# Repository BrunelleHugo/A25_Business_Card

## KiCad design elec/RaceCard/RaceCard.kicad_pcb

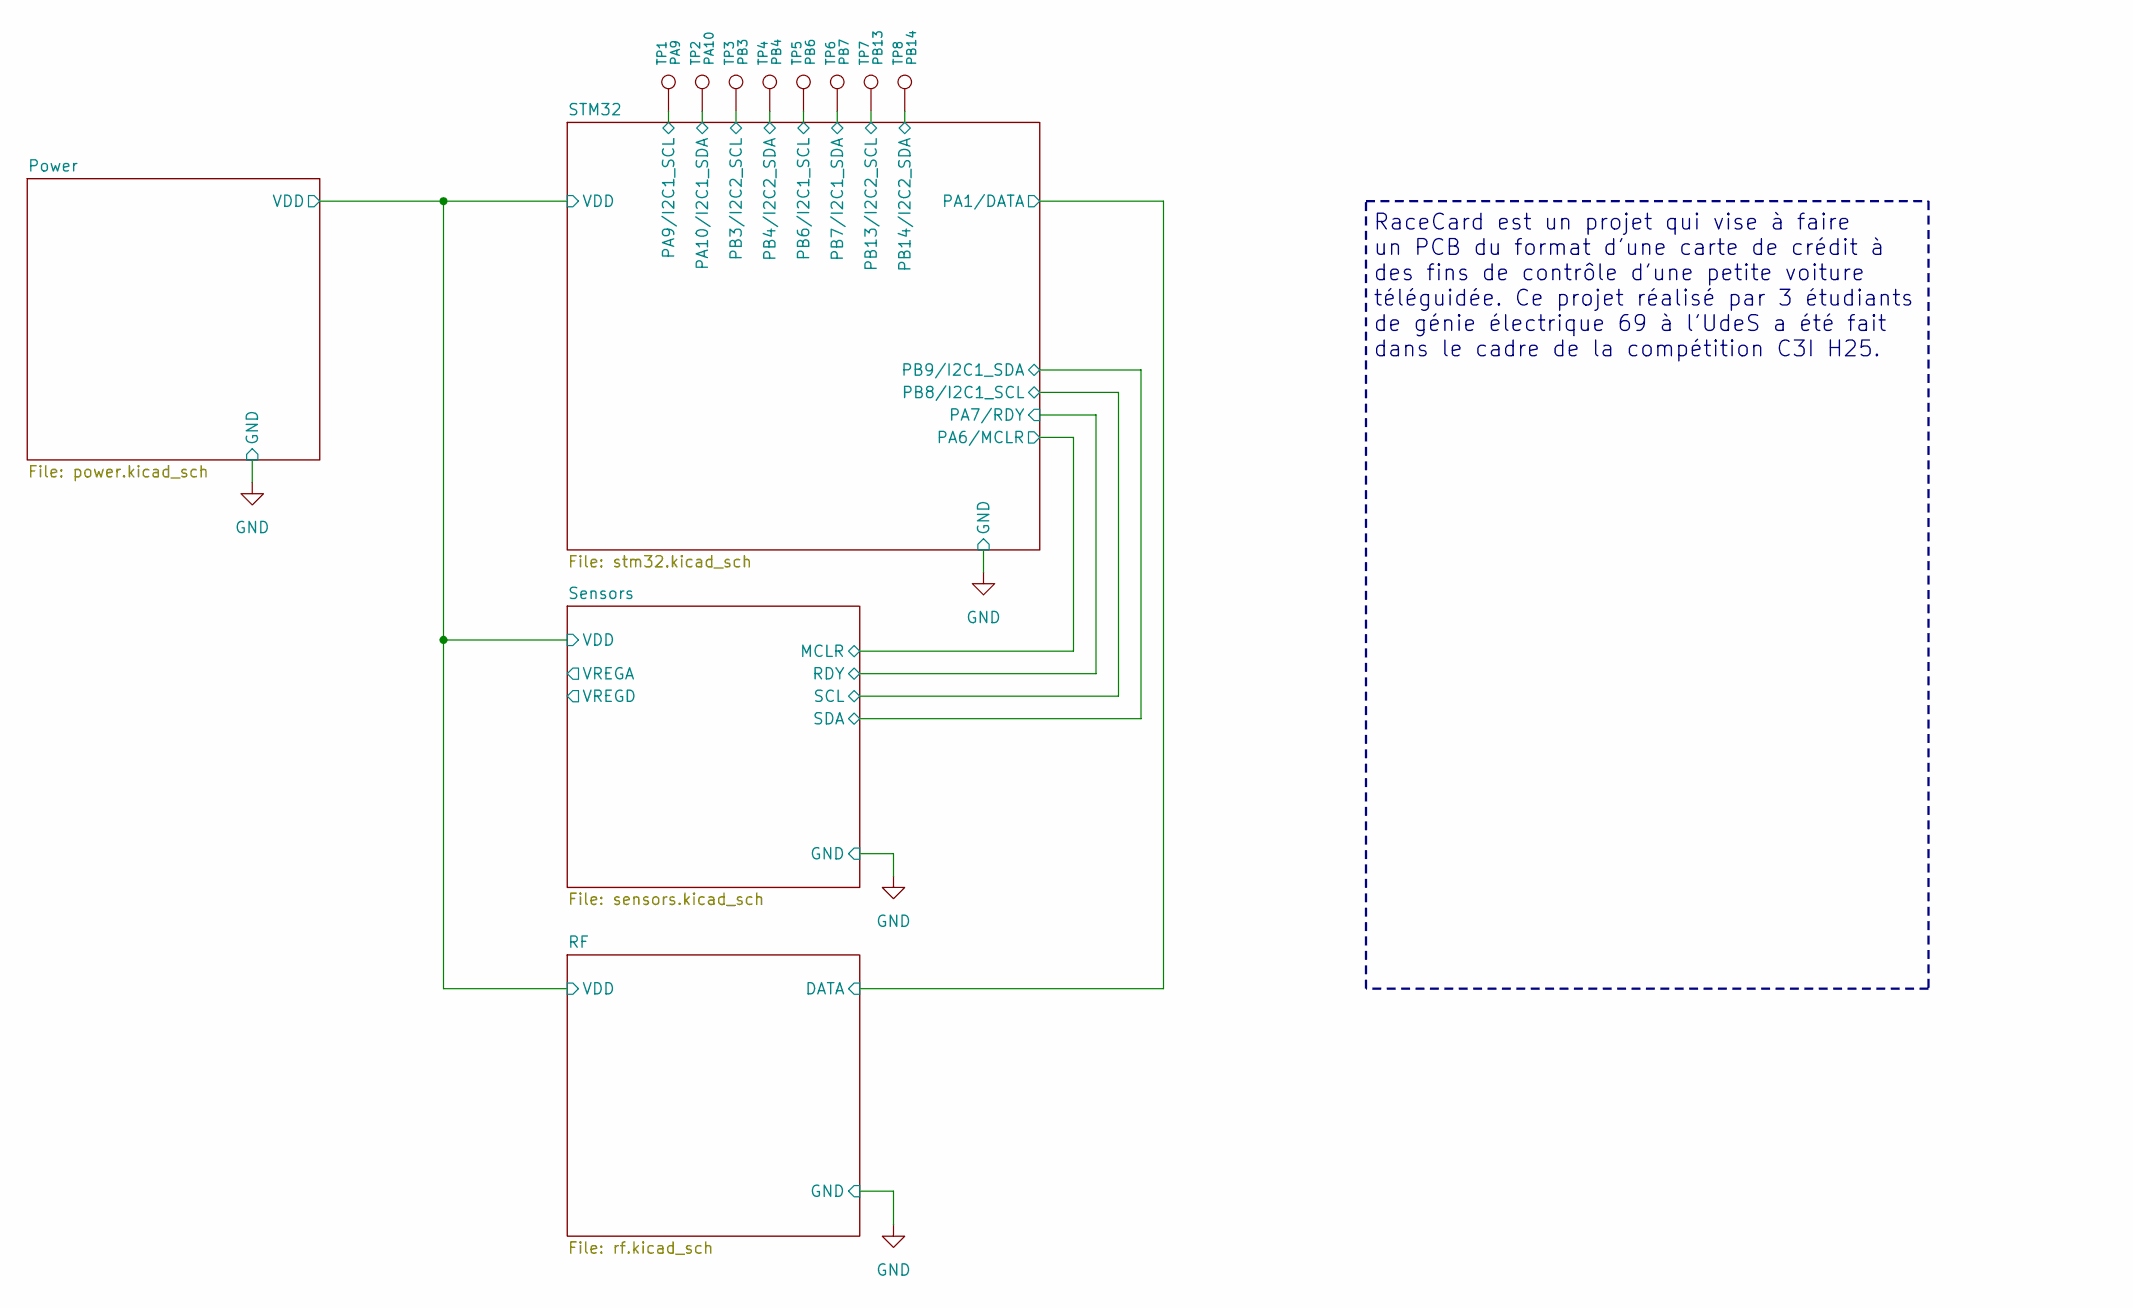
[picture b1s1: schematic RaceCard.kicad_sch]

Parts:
TP1: PA9; TestPoint_Pad_2.0x2.0mm
TP2: PA10; TestPoint_Pad_2.0x2.0mm
TP3: PB3; TestPoint_Pad_2.0x2.0mm
TP4: PB4; TestPoint_Pad_2.0x2.0mm
TP5: PB6; TestPoint_Pad_2.0x2.0mm
TP6: PB7; TestPoint_Pad_2.0x2.0mm
TP7: PB13; TestPoint_Pad_2.0x2.0mm
TP8: PB14; TestPoint_Pad_2.0x2.0mm

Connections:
/STM32/PA9/I2C1_SCL: TP1.1; also elsewhere on the board
/STM32/PA10/I2C1_SDA: TP2.1; also elsewhere on the board
/STM32/PB3/I2C2_SCL: TP3.1; also elsewhere on the board
/STM32/PB4/I2C2_SDA: TP4.1; also elsewhere on the board
/STM32/PB6/I2C1_SCL: TP5.1; also elsewhere on the board
/STM32/PB7/I2C1_SDA: TP6.1; also elsewhere on the board
/STM32/PB13/I2C2_SCL: TP7.1; also elsewhere on the board
/STM32/PB14/I2C2_SDA: TP8.1; also elsewhere on the board

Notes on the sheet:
RaceCard est un projet qui vise à faire un PCB du format d'une carte de crédit à des fins de contrôle d'une petite voiture téléguidée. Ce projet réalisé par 3 étudiants de génie électrique 69 à l'UdeS a été fait dans le cadre de la compétition C3I H25.

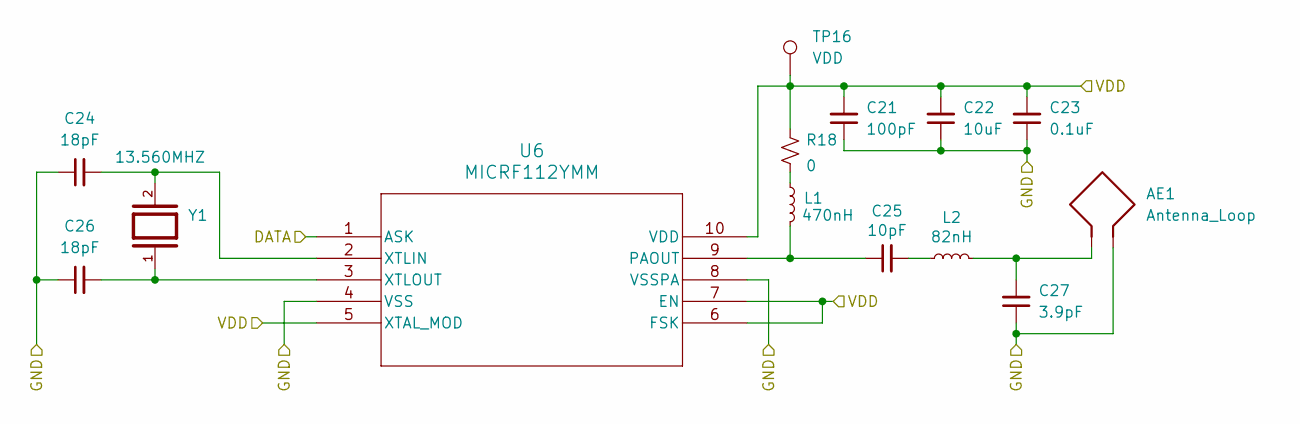
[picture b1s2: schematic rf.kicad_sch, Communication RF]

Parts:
AE1: Antenna_Loop
C21: 100pF; C_0603_1608Metric
C22: 10uF; C_0603_1608Metric
C23: 0.1uF; C_0603_1608Metric
C24, C26: 18pF; C_0603_1608Metric
C25: 10pF; C_0603_1608Metric
C27: 3.9pF; C_0603_1608Metric
L1: 470nH; L_0603_1608Metric
L2: 82nH; L_0603_1608Metric
R18: 0; R_0603_1608Metric
TP16: VDD; TestPoint_THTPad_3.0x3.0mm_Drill1.5mm
U6: MICRF112YMM; MSOP10_MC_MCH
Y1: 13.560MHZ; XTAL_ABLS-13.560MHZ-10-R20-D-T; PARTREV 02.16.2021

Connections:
/Power/VDD: C21.2, C22.2, C23.2, R18.1, TP16.1, U6.5 (XTAL_MOD), U6.6 (FSK), U6.7 (EN), U6.10 (VDD); also elsewhere on the board
/RF/DATA: U6.1 (ASK); also elsewhere on the board
GND: C21.1, C22.1, C23.1, C24.1, C26.1, C27.1, U6.4 (VSS), U6.8 (VSSPA); also elsewhere on the board
unnamed: C27.2, L2.2
unnamed: C25.2, L2.1
unnamed: L1.1, R18.2
unnamed: C25.1, L1.2, U6.9 (PAOUT)
unnamed: C24.2, U6.2 (XTLIN), Y1.2
unnamed: C26.2, U6.3 (XTLOUT), Y1.1

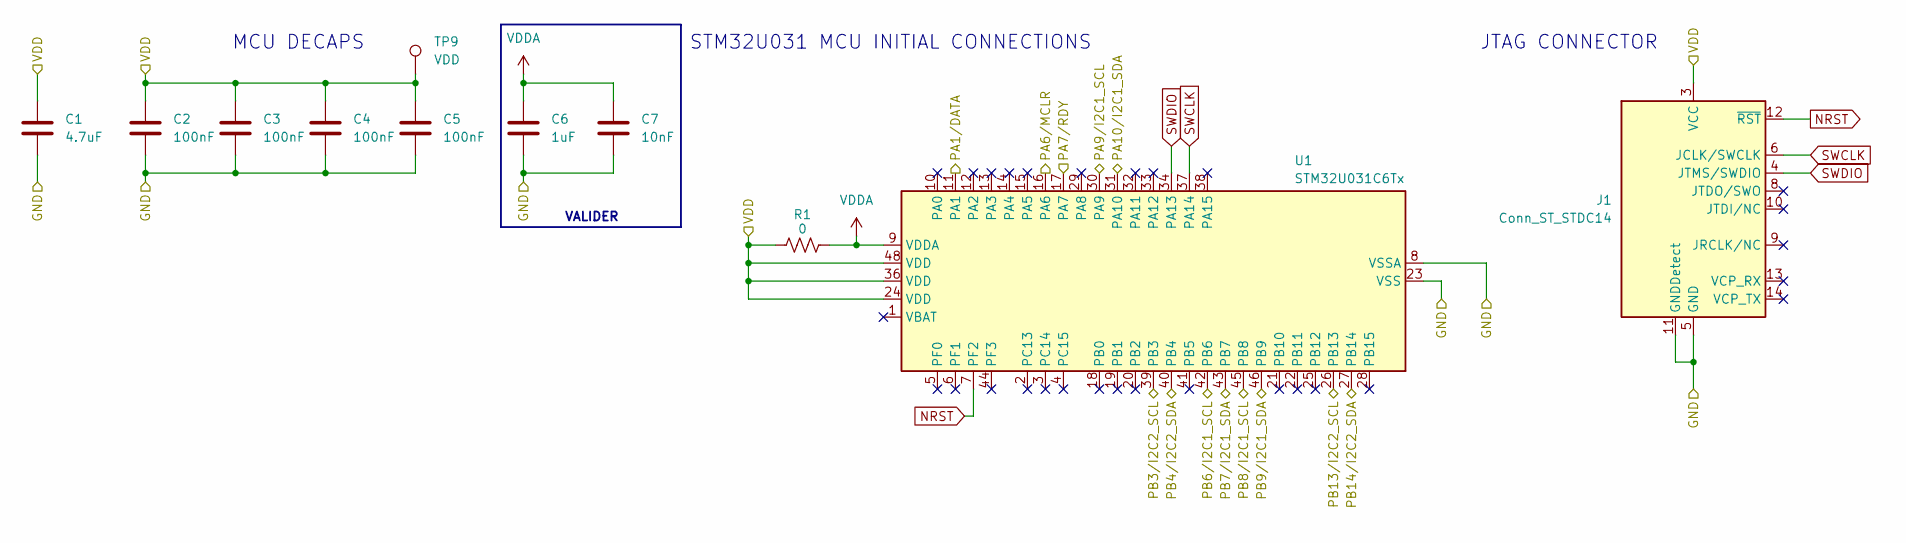
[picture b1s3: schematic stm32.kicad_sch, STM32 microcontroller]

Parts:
C1: 4.7uF; C_0603_1608Metric
C2, C3, C4, C5: 100nF; C_0603_1608Metric
C6: 1uF; C_0603_1608Metric
C7: 10nF; C_0603_1608Metric
J1: Conn_ST_STDC14; CONN_3020-14-0300-00_CNC
R1: 0; R_0603_1608Metric
TP9: VDD; TestPoint_THTPad_3.0x3.0mm_Drill1.5mm
U1: STM32U031C6Tx; LQFP-48_7x7mm_P0.5mm

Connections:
/Power/VDD: C1.1, C2.1, C3.1, C4.1, C5.1, J1.3 (VCC), R1.1, TP9.1, U1.24 (VDD), U1.36 (VDD), U1.48 (VDD); also elsewhere on the board
/RF/DATA: U1.11 (PA1); also elsewhere on the board
/STM32/PA6/MCLR: U1.16 (PA6); also elsewhere on the board
/STM32/PA7/RDY: U1.17 (PA7); also elsewhere on the board
/STM32/PA9/I2C1_SCL: U1.30 (PA9); also elsewhere on the board
/STM32/PA10/I2C1_SDA: U1.31 (PA10); also elsewhere on the board
/STM32/PB3/I2C2_SCL: U1.39 (PB3); also elsewhere on the board
/STM32/PB4/I2C2_SDA: U1.40 (PB4); also elsewhere on the board
/STM32/PB6/I2C1_SCL: U1.42 (PB6); also elsewhere on the board
/STM32/PB7/I2C1_SDA: U1.43 (PB7); also elsewhere on the board
/STM32/PB8/I2C1_SCL: U1.45 (PB8); also elsewhere on the board
/STM32/PB9/I2C1_SDA: U1.46 (PB9); also elsewhere on the board
/STM32/PB13/I2C2_SCL: U1.26 (PB13); also elsewhere on the board
/STM32/PB14/I2C2_SDA: U1.27 (PB14); also elsewhere on the board
GND: C1.2, C2.2, C3.2, C4.2, C5.2, C6.2, C7.2, J1.5 (GND), J1.7 (GND), J1.11 (GNDDetect), U1.8 (VSSA), U1.23 (VSS), U1.35 (VSS), U1.47 (VSS); also elsewhere on the board
NRST: J1.12 (~RST), U1.7 (PF2)
SWCLK: J1.6 (JCLK/SWCLK), U1.37 (PA14)
SWDIO: J1.4 (JTMS/SWDIO), U1.34 (PA13)
VDDA: C6.1, C7.1, R1.2, U1.9 (VDDA)

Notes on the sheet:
MCU DECAPS
JTAG CONNECTOR
VALIDER
STM32U031 MCU INITIAL CONNECTIONS

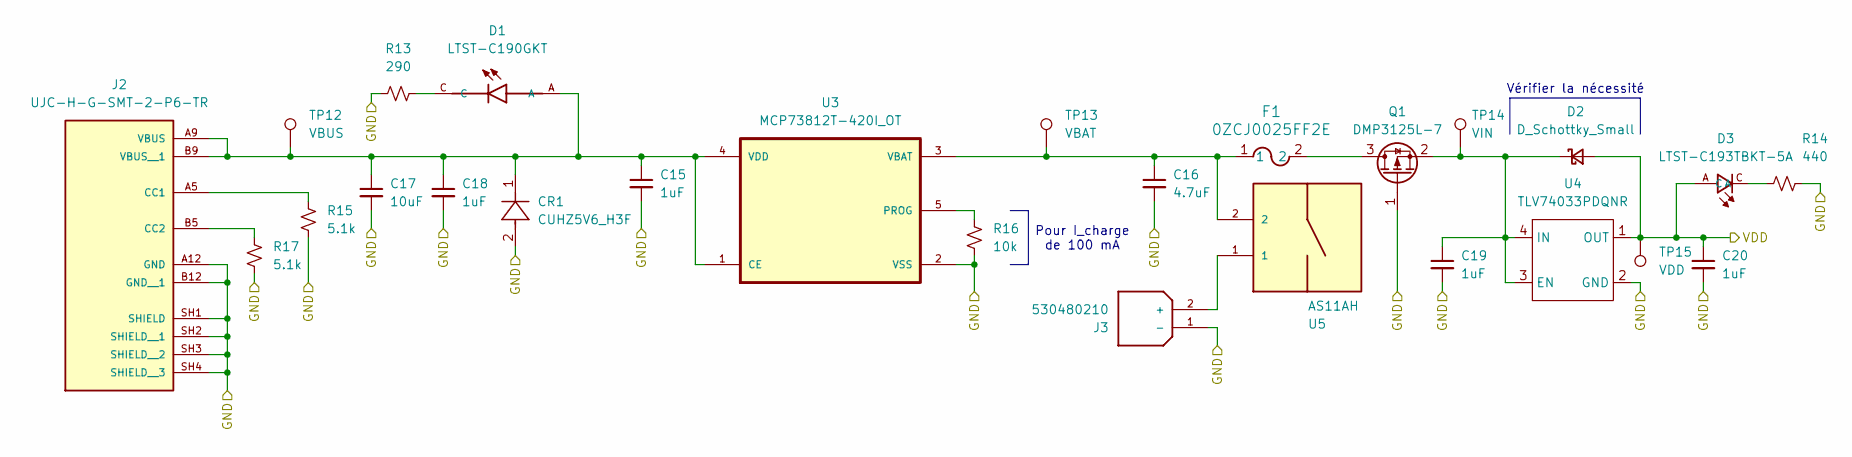
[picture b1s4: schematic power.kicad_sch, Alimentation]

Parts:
C15, C18, C19, C20: 1uF; C_0603_1608Metric
C16: 4.7uF; C_0603_1608Metric
C17: 10uF; C_0603_1608Metric
CR1: CUHZ5V6_H3F; SOD-323HEUS2H_TOS
D1: LTST-C190GKT; LEDM1608X80
D2: D_Schottky_Small; D_0603_1608Metric
D3: LTST-C193TBKT-5A; LEDM1608X80
F1: 0ZCJ0025FF2E; 0ZCJ_BEL
J2: UJC-H-G-SMT-2-P6-TR; SAMESKY_UJC-H-G-SMT-2-P6-TR; PARTREV 1.0
J3: 530480210; MOLEX_530480210; PARTREV A
Q1: DMP3125L-7; SOT91P240X110-3N
R13: 290; R_0603_1608Metric
R14: 440; R_0603_1608Metric
R15, R17: 5.1k; R_0603_1608Metric
R16: 10k; R_0603_1608Metric
TP12: VBUS; TestPoint_THTPad_3.0x3.0mm_Drill1.5mm
TP13: VBAT; TestPoint_THTPad_3.0x3.0mm_Drill1.5mm
TP14: VIN; TestPoint_THTPad_3.0x3.0mm_Drill1.5mm
TP15: VDD; TestPoint_THTPad_3.0x3.0mm_Drill1.5mm
U3: MCP73812T-420I_OT; SOT95P280X145-5N
U4: TLV74033PDQNR; SUP_TPS3831L30DQNR
U5: AS11AH

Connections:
/Power/VDD: C20.1, D2.2 (A), D3.A, TP15.1, U4.1 (OUT); also elsewhere on the board
GND: C15.2, C16.2, C17.2, C18.2, C19.2, C20.2, CR1.2, J2.A12 (GND), J2.B12 (GND__1), J2.SH1 (SHIELD), J2.SH2 (SHIELD__1), J2.SH3 (SHIELD__2), J2.SH4 (SHIELD__3), J3.1 (-), Q1.1 (G), R13.1, R14.2, R15.1, R16.2, R17.2, U3.2 (VSS), U4.2 (GND); also elsewhere on the board
unnamed: D1.C, R13.2
unnamed: C19.1, D2.1 (K), Q1.2 (S), TP14.1, U4.3 (EN), U4.4 (IN)
unnamed: D3.C, R14.1
unnamed: J2.A5 (CC1), R15.2
unnamed: J2.B5 (CC2), R17.1
unnamed: C15.1, C17.1, C18.1, CR1.1, D1.A, J2.A9 (VBUS), J2.B9 (VBUS__1), TP12.1, U3.1 (CE), U3.4 (VDD)
unnamed: J3.2 (+), U5.1
unnamed: F1.2, Q1.3 (D)
unnamed: R16.1, U3.5 (PROG)
unnamed: C16.1, F1.1, TP13.1, U3.3 (VBAT), U5.2

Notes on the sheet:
Vérifier la nécessité
Pour I_charge de 100 mA

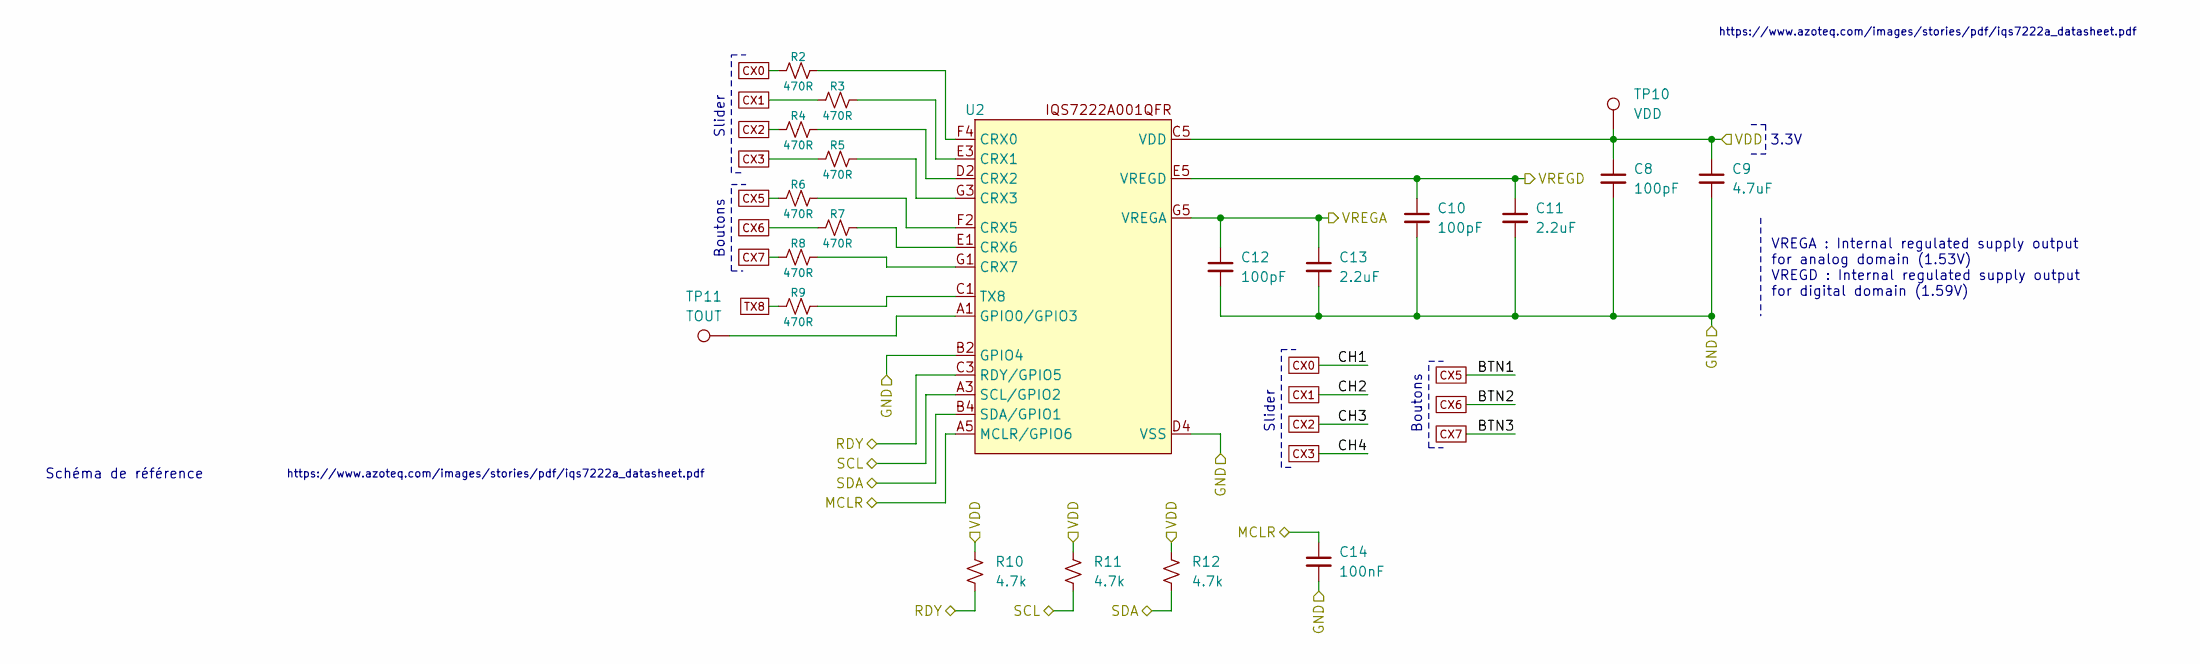
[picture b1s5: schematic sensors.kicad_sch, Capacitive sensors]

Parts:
C8, C10, C12: 100pF; C_0603_1608Metric
C9: 4.7uF; C_0603_1608Metric
C11, C13: 2.2uF; C_0603_1608Metric
C14: 100nF; C_0603_1608Metric
R2, R3, R4, R5, R6, R7, R8, R9: 470R; R_0603_1608Metric
R10, R11, R12: 4.7k; R_0603_1608Metric
TP10: VDD; TestPoint_THTPad_3.0x3.0mm_Drill1.5mm
TP11: TOUT; TestPoint_THTPad_3.0x3.0mm_Drill1.5mm
U2: IQS7222A001QFR; IQS7222A001CSR

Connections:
/Power/VDD: C8.1, C9.1, R10.1, R11.1, R12.1, TP10.1, U2.C5 (VDD); also elsewhere on the board
/STM32/PA6/MCLR: C14.1, U2.A5 (MCLR/GPIO6); also elsewhere on the board
/STM32/PA7/RDY: R10.2, U2.C3 (RDY/GPIO5); also elsewhere on the board
/STM32/PB8/I2C1_SCL: R11.2, U2.A3 (SCL/GPIO2); also elsewhere on the board
/STM32/PB9/I2C1_SDA: R12.2, U2.B4 (SDA/GPIO1); also elsewhere on the board
/Sensors/VREGA: C12.1, C13.1, U2.G5 (VREGA)
/Sensors/VREGD: C10.1, C11.1, U2.E5 (VREGD)
CX0: R2.1
CX1: R3.1
CX2: R4.1
CX3: R5.1
CX5: R6.1
CX6: R7.1
CX7: R8.1
GND: C8.2, C9.2, C10.2, C11.2, C12.2, C13.2, C14.2, U2.B2 (GPIO4), U2.D4 (VSS); also elsewhere on the board
unnamed: R2.2, U2.F4 (CRX0)
unnamed: R3.2, U2.E3 (CRX1)
unnamed: R4.2, U2.D2 (CRX2)
unnamed: R5.2, U2.G3 (CRX3)
unnamed: R6.2, U2.F2 (CRX5)
unnamed: R7.2, U2.E1 (CRX6)
unnamed: R8.2, U2.G1 (CRX7)
unnamed: TP11.1, U2.A1 (GPIO0/GPIO3)
unnamed: R9.2, U2.C1 (TX8)
TX8: R9.1

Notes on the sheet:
VREGA : Internal regulated supply output for analog domain (1.53V) VREGD : Internal regulated supply output for digital domain (1.59V)
Slider
Schéma de référence
https://www.azoteq.com/images/stories/pdf/iqs7222a_datasheet.pdf
Boutons
3.3V

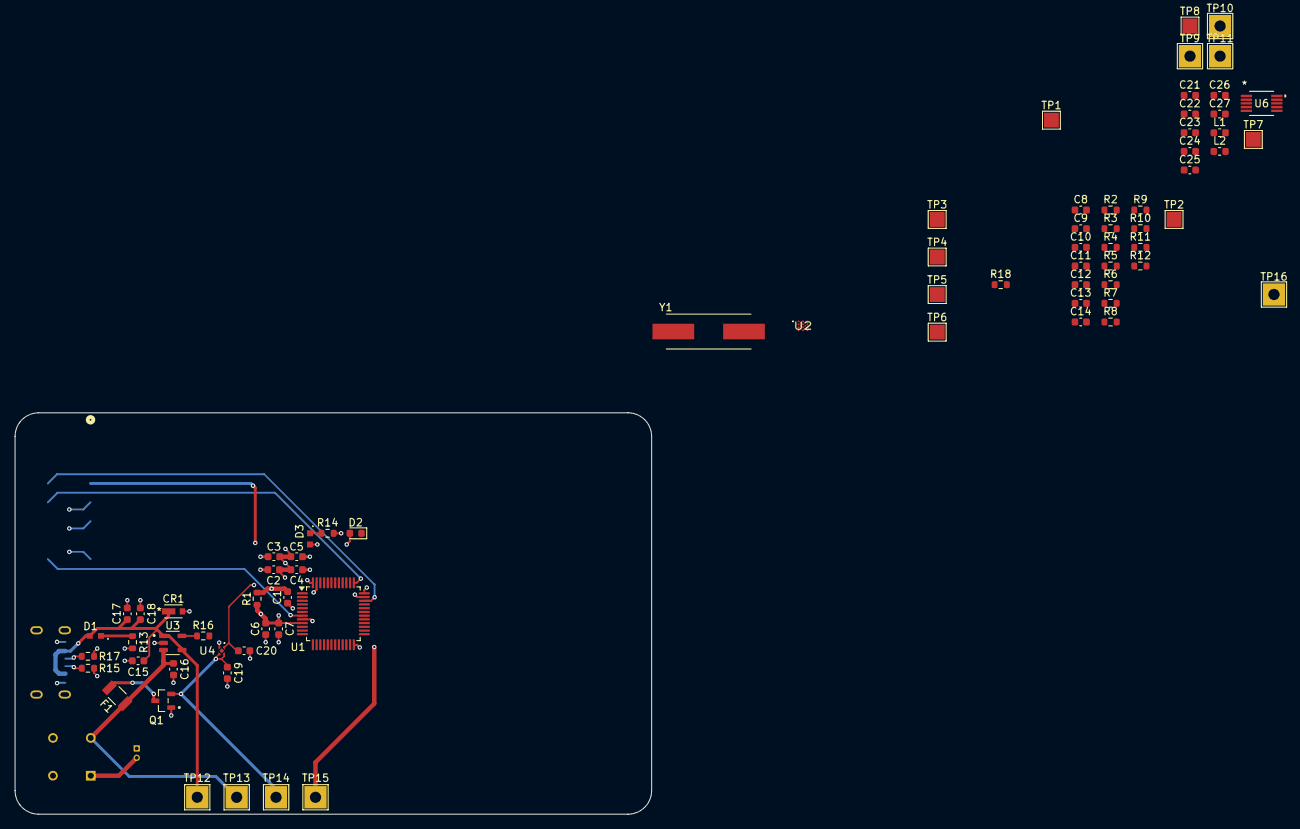
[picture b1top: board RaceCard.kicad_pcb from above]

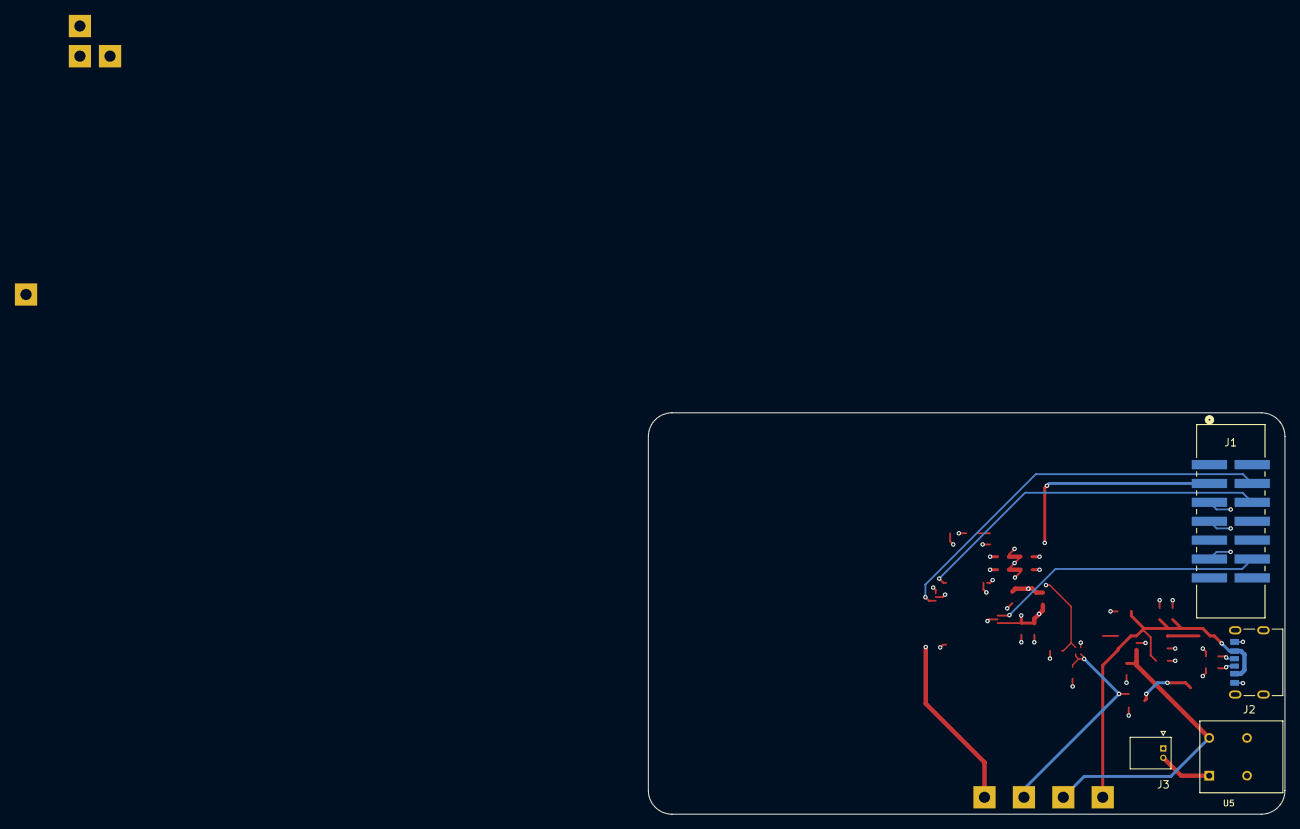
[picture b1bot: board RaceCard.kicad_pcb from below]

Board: 4 copper layers, 85.6 x 54.0 mm, 79 parts (4 on the bottom side), 46 nets.

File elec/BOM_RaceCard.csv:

Reference;Qty;Value;DNP;Exclude from BOM;Exclude from Board;Footprint;Datasheet
AE1;1;Antenna_Loop;;;;;~
C1,C9,C16;3;4.7uF;;;;Capacitor_SMD:C_0603_1608Metric;~
C2,C3,C4,C5,C14;5;100nF;;;;Capacitor_SMD:C_0603_1608Metric;~
C6,C15,C18,C19,C20;5;1uF;;;;Capacitor_SMD:C_0603_1608Metric;~
C7;1;10nF;;;;Capacitor_SMD:C_0603_1608Metric;~
C8,C10,C12,C21;4;100pF;;;;Capacitor_SMD:C_0603_1608Metric;~
C11,C13;2;2.2uF;;;;Capacitor_SMD:C_0603_1608Metric;~
C17,C22;2;10uF;;;;Capacitor_SMD:C_0603_1608Metric;~
C23;1;0.1uF;;;;Capacitor_SMD:C_0603_1608Metric;~
C24,C26;2;18pF;;;;Capacitor_SMD:C_0603_1608Metric;~
C25;1;10pF;;;;Capacitor_SMD:C_0603_1608Metric;~
C27;1;3.9pF;;;;Capacitor_SMD:C_0603_1608Metric;~
CR1;1;CUHZ5V6_H3F;;;;C3I_A25:SOD-323HEUS2H_TOS;https://toshiba.semicon-storage.com/info/docget.jsp?did=1415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
D1;1;LTST-C190GKT;;;;LTST-C190GKT:LEDM1608X80;
D2;1;D_Schottky_Small;;;;;~
D3;1;LTST-C193TBKT-5A;;;;LTST-C193TBKT-5A:0603;
F1;1;0ZCJ0025FF2E;;;;C3I_A25:0ZCJ_BEL;0ZCJ0025FF2E
J1;1;Conn_ST_STDC14;;;;C3I_A25:CONN_3020-14-0300-00_CNC;https://www.cnctech.us/pdfs/3020-XX-0300-00%20(9T).pdf
J2;1;UJC-H-G-SMT-2-P6-TR;;;;UJC-H-G-SMT-2-P6-TR:SAMESKY_UJC-H-G-SMT-2-P6-TR;
J3;1;530480210;;;;530480210:MOLEX_530480210;
L1;1;470nH;;;;Inductor_SMD:L_0603_1608Metric;~
L2;1;82nH;;;;Inductor_SMD:L_0603_1608Metric;~
Q1;1;DMP3125L-7;;;;C3I_A25:SOT91P240X110-3N;~
R1,R19;2;0;;;;Resistor_SMD:R_0603_1608Metric;~
R2,R3,R4,R5,R6,R7,R8,R9,R10;9;470R;;;;Resistor_SMD:R_0603_1608Metric;~
R11,R12,R13;3;4.7k;;;;Resistor_SMD:R_0603_1608Metric;~
R14;1;290;;;;Resistor_SMD:R_0603_1608Metric;~
R15;1;440;;;;Resistor_SMD:R_0603_1608Metric;~
R16,R18;2;5.1k;;;;Resistor_SMD:R_0603_1608Metric;~
R17;1;10k;;;;Resistor_SMD:R_0603_1608Metric;~
TP1,TP2,TP6,TP7;4;VDD;;;;TestPoint:TestPoint_THTPad_3.0x3.0mm_Drill1.5mm;~
TP3;1;VBUS;;;;TestPoint:TestPoint_THTPad_3.0x3.0mm_Drill1.5mm;~
TP4;1;VBAT;;;;TestPoint:TestPoint_THTPad_3.0x3.0mm_Drill1.5mm;~
TP5;1;VIN;;;;TestPoint:TestPoint_THTPad_3.0x3.0mm_Drill1.5mm;~
TP8;1;PA9;;;;TestPoint:TestPoint_Pad_2.0x2.0mm;~
TP9;1;PA10;;;;TestPoint:TestPoint_Pad_2.0x2.0mm;~
TP10;1;PB3;;;;TestPoint:TestPoint_Pad_2.0x2.0mm;~
TP11;1;PB4;;;;TestPoint:TestPoint_Pad_2.0x2.0mm;~
TP12;1;PB6;;;;TestPoint:TestPoint_Pad_2.0x2.0mm;~
TP13;1;PB7;;;;TestPoint:TestPoint_Pad_2.0x2.0mm;~
TP14;1;PB13;;;;TestPoint:TestPoint_Pad_2.0x2.0mm;~
TP15;1;PB14;;;;TestPoint:TestPoint_Pad_2.0x2.0mm;~
U1;1;STM32U031C6Tx;;;;Package_QFP:LQFP-48_7x7mm_P0.5mm;https://www.st.com/resource/en/datasheet/stm32u031c6.pdf
U2;1;IQS7222A001QFR;;;;;
U3;1;MCP73812T-420I_OT;;;;MCP73812T-420I_OT:SOT95P280X145-5N;
U4;1;TLV74033PDQNR;;;;C3I_A25:SUP_TPS3831L30DQNR;
U5;1;AS11AH;;;;AS11AH:AS11AH;
U6;1;MICRF112YMM;;;;MSOP10_MC_MCH;MICRF112YMM
Y1;1;13.560MHZ;;;;ABLS-13.560MHZ-10-R20-D-T:XTAL_ABLS-13.560MHZ-10-R20-D-T;

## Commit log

2025-10-04 Update .gitignore (vide)
2025-10-04 Remove
2025-10-04 + doc pour capacitive sensors
2025-10-20 move doc
2025-10-21 + blank project
2025-10-21 + lib C3I_A25 et IQS7222A001QFR
    ajout de IQS7222A001QFR dans le sch de sensors
2025-10-27 schematic slider + btns (à valider)
2025-11-10 Ajout du schéma pour TX
2025-11-10 ajout de reverse polarity et efuse
2025-11-30 V1 du chargeur fini
    Valider par qqn d'autre que Hugo
2025-11-30 déplacement de l'image
2025-11-30 Ajout fichiers de bases pour la voiture
2025-11-30 Ajout du schema à gab
2025-11-30 petit déplacement
2025-11-30 Choses manquantes
2025-11-30 Commence plugger choses
2025-12-01 Modif
2025-12-01 ajout connecteur usb c et leds
2025-12-01 Ajout du rx
2025-12-01 + connections stm et autres
2025-12-01 + test points
2025-12-01 petite surprise
2025-12-01 + BOM
2025-12-02 Ajout du power et du stm
2025-12-06 Fix des footprints et edge cuts
2025-12-12 Tout le power est routed
2026-01-04 BOMs
2026-01-05 powerpoint
2026-01-15 Power net update et cleanup sch
2026-01-20 Manque juste RF
2026-01-20 Cleanup
